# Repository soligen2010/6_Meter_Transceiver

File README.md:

# 6_Meter_Transceiver
A homebrew transceiver for the 6 meter Ham band
 
This project is work in progress.

## 2022-2-27 Status
 
This is my 6 Meter homebrew transceiver, currently work in progress.  It is a single conversion super –heterodyne design.  I constructed each stage independently with SMA connectors.  This is so I can re-make sections as needed, and will allow me in the future to swap sections to experiment with alternate designs.  The VFO and BFO are controlled using a SI5351 with an Arduino micro controller.  I currently have separate SI5351 modules for VFO and BFO because I suspected issues with cross-talk.  These issues may not actually be real, so once I am happy with the performance, I will test again with just one module to see if it is OK.  The Power Amp is still on the to-do list, so output is well under 0 DBm

The Blue boards were designed by me and ordered on-line.  The other boards I etched myself.  Construction is mostly surface mount because I find it easier than drilling all the holes.  SMD components are mostly 805 and 1206 size. Transistors are SOT23.

The Band Pass filter is a 5 coil design made with air-core inductors.

3 bi-directional termination insensitive (TIA) amps are used (blue boards).  Total RX gain is about 44db.  Total TX gain is about 16db.  Each board has its own independent RX/TX switching circuitry (mosfet based) and is fed with +12.5, GND, and RX/TX logic signal from the Arduino (3V logic and up will work)
The Mixer and modulator are both Diode Ring mixers.

The 12 MHz SSB filter is a crystal ladder filter similar to the one used in the uBitx.

The Mic and audio pre-amp (also a blue board) is made on a modified TIA amp board.  I had 10 of these boards made, and the needed circuitry was largely the same, so I modified the board with a rotary tool and jumpers.

The Audio amp is a PAM8403 module and drives a headset.  I did make some modifications to the module so it runs in-spec and to eliminate the power on audio pop.

The challenges I have been having are mostly related to spurs, splatter, carrier suppression and TX audio quality.  I have been gradually tweaking these things to improve operation before I start on a power amp.  My IF is 12 MHZ, and I was using the LSB side of the crystal filter because it is sharper (VFO 62 – 66 MHz) but have recently changed over to the USB side of the filter (VFO 38 – 42 MHz).  This eliminated the spurs I was seeing near the pass band.  I still need to make some adjustments to the crystal filter as it is too broad.

I still have some splatter and audio quality seems low, but I am starting to doubt my test setup.  I see the splatter on the RTL SDR, but I don’t see it on the Tiny SA.  The spatter happens at ~160 KHz intervals.  I am hoping to find someone local with a better spectrum analyzer to help me verify if it is the rig or my SDR dongle/test setup.

The modules to the side of the picture are my rejects/experiments.  The one covered in copper shows how I eventually will shield all the modules.  I 3D printed a cover for the board, then wrapped it with copper tape, soldered to the bottom ground plane.  The one shown is a diode ring modulator.  For some unknown reason the carrier suppression is rather poor.  I had previously made a junk-box modulator that had much better carrier suppression.  I don’t know why it is better than the one I more carefully made for the radio, but until I figure it out, I am using the junk box version.  The junk box modulator uses unmatched schottkey diodes, whereas the “final” one uses a 4 diode SMD package because I wanted them matched – I thought this would be better, but maybe not.

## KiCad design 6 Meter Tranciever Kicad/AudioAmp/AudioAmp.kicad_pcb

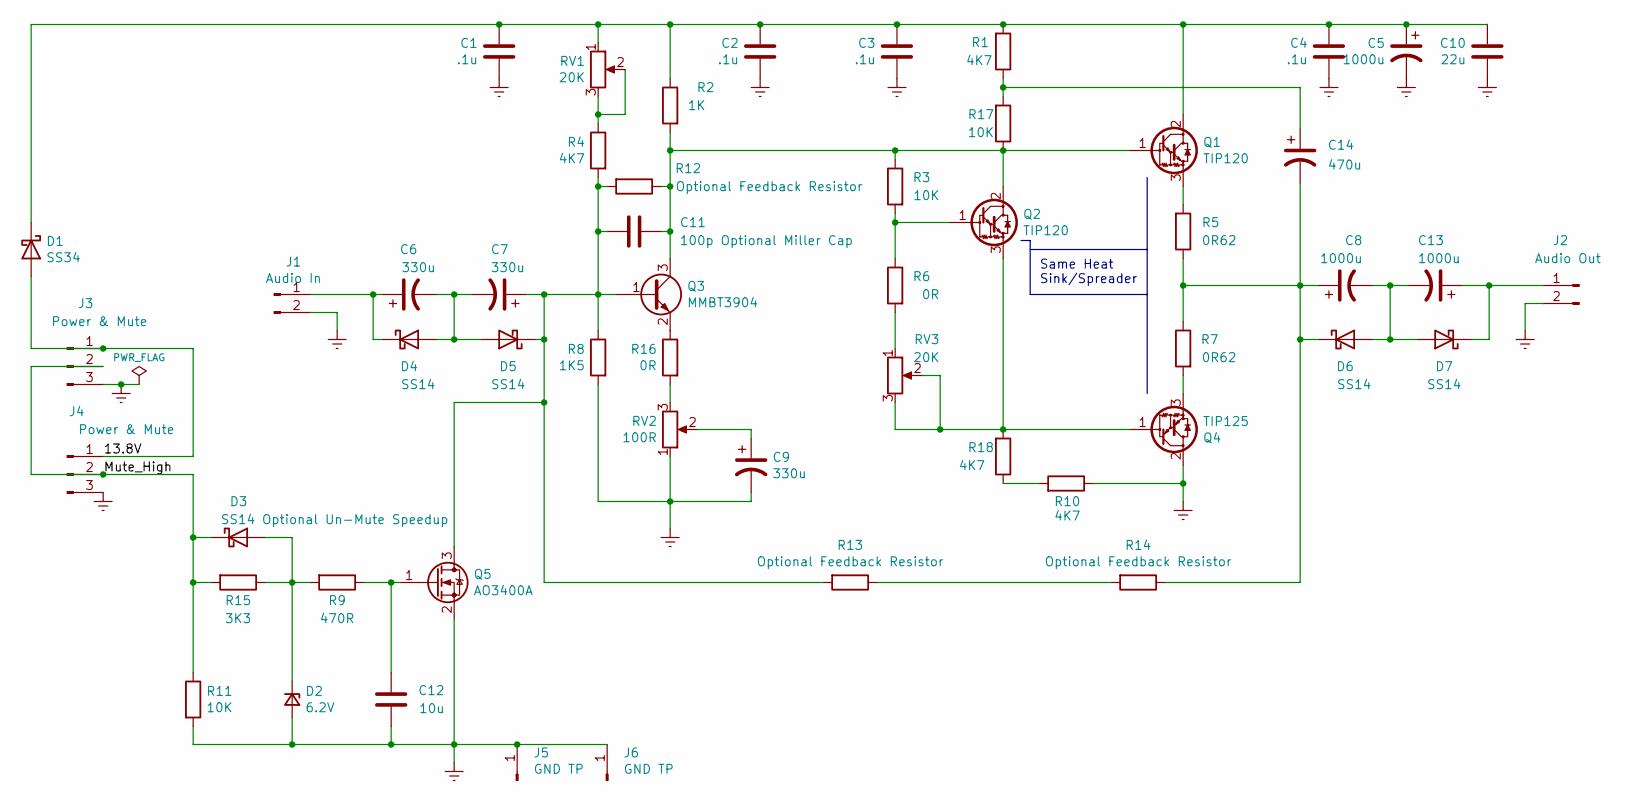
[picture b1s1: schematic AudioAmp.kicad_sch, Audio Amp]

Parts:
C1, C2, C3, C4: .1u; SMD_Combo_1206_0805
C5: 1000u; CP_Radial_D18.0mm_P7.50mm
C6, C7, C9: 330u; CP_Radial_D13.0mm_P5.00mm
C8, C13: 1000u; CP_Radial_D13.0mm_P5.00mm
C10: 22u; SMD_Combo_1206_0805
C11: 100p Optional Miller Cap; SMD_Combo_1206_0805
C12: 10u; SMD_Combo_1206_0805
C14: 470u; CP_Radial_D13.0mm_P5.00mm
D1: SS34; D_SMA_Handsoldering
D2: 6.2V; D_MiniMELF_Handsoldering
D3: SS14 Optional Un-Mute Speedup; D_SMA_Handsoldering
D4, D5, D6, D7: SS14; D_SMA_Handsoldering
J1: Audio In; Molex_KK-254_AE-6410-02A_1x02_P2.54mm_Vertical
J2: Audio Out; Molex_KK-254_AE-6410-02A_1x02_P2.54mm_Vertical
J3, J4: Power & Mute; FanPinHeader_1x03_P2.54mm_Vertical
J5, J6: GND TP; PinHeader_1x01_P2.54mm_Vertical
Q1, Q2: TIP120; TO-220-3_Vertical
Q3: MMBT3904; SOT-23_Handsoldering
Q4: TIP125; TO-220-3_Vertical
Q5: AO3400A; SOT-23_Handsoldering
R1, R4, R10, R18: 4K7; SMD_Combo_1206_0805
R2: 1K; SMD_Combo_1206_0805
R3, R11, R17: 10K; SMD_Combo_1206_0805
R5, R7: 0R62; R_Axial_DIN0309_L9.0mm_D3.2mm_P12.70mm_Horizontal
R6, R16: 0R; SMD_Combo_1206_0805
R8: 1K5; SMD_Combo_1206_0805
R9: 470R; SMD_Combo_1206_0805
R12, R13, R14: Optional Feedback Resistor; SMD_Combo_1206_0805
R15: 3K3; SMD_Combo_1206_0805
RV1, RV3: 20K; Potentiometer_Piher_PT-6-V_Vertical
RV2: 100R; Potentiometer_Piher_PT-6-V_Vertical

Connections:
/13.8V: D1.2 (A), J3.1, J4.1
/Mute_High: D3.1 (K), J3.2, J4.2, R11.1, R15.2
GNDREF: C1.2, C2.2, C3.2, C4.2, C5.2, C9.2, C10.2, C12.2, D2.2 (A), J1.2, J2.2, J3.3, J4.3, J5.1, J6.1, Q4.2 (C), Q5.2 (S), R8.2, R10.1, R11.2, RV2.1
unnamed: C1.1, C2.1, C3.1, C4.1, C5.1, C10.1, D1.1 (K), Q1.2 (C), R1.2, R2.1, RV1.1
unnamed: C6.1, D4.1 (K), J1.1
unnamed: C6.2, C7.2, D4.2 (A), D5.2 (A)
unnamed: C8.1, C14.2, D6.1 (K), R5.1, R7.1, R14.1
unnamed: C9.1, RV2.2
unnamed: C11.1, Q1.1 (B), Q2.2 (C), Q3.3 (C), R2.2, R3.1, R12.1, R17.1
unnamed: C7.1, C11.2, D5.1 (K), Q3.1 (B), Q5.3 (D), R4.2, R8.1, R12.2, R13.2
unnamed: C12.1, Q5.1 (G), R9.1
unnamed: C13.1, D7.1 (K), J2.1
unnamed: C8.2, C13.2, D6.2 (A), D7.2 (A)
unnamed: C14.1, R1.1, R17.2
unnamed: D2.1 (K), D3.2 (A), R9.2, R15.1
unnamed: Q1.3 (E), R5.2
unnamed: Q2.1 (B), R3.2, R6.1
unnamed: Q2.3 (E), Q4.1 (B), R18.2, RV3.2, RV3.3
unnamed: Q3.2 (E), R16.1
unnamed: Q4.3 (E), R7.2
unnamed: R4.1, RV1.2, RV1.3
unnamed: R6.2, RV3.1
unnamed: R10.2, R18.1
unnamed: R13.1, R14.2
unnamed: R16.2, RV2.3

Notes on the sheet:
Same Heat Sink/Spreader

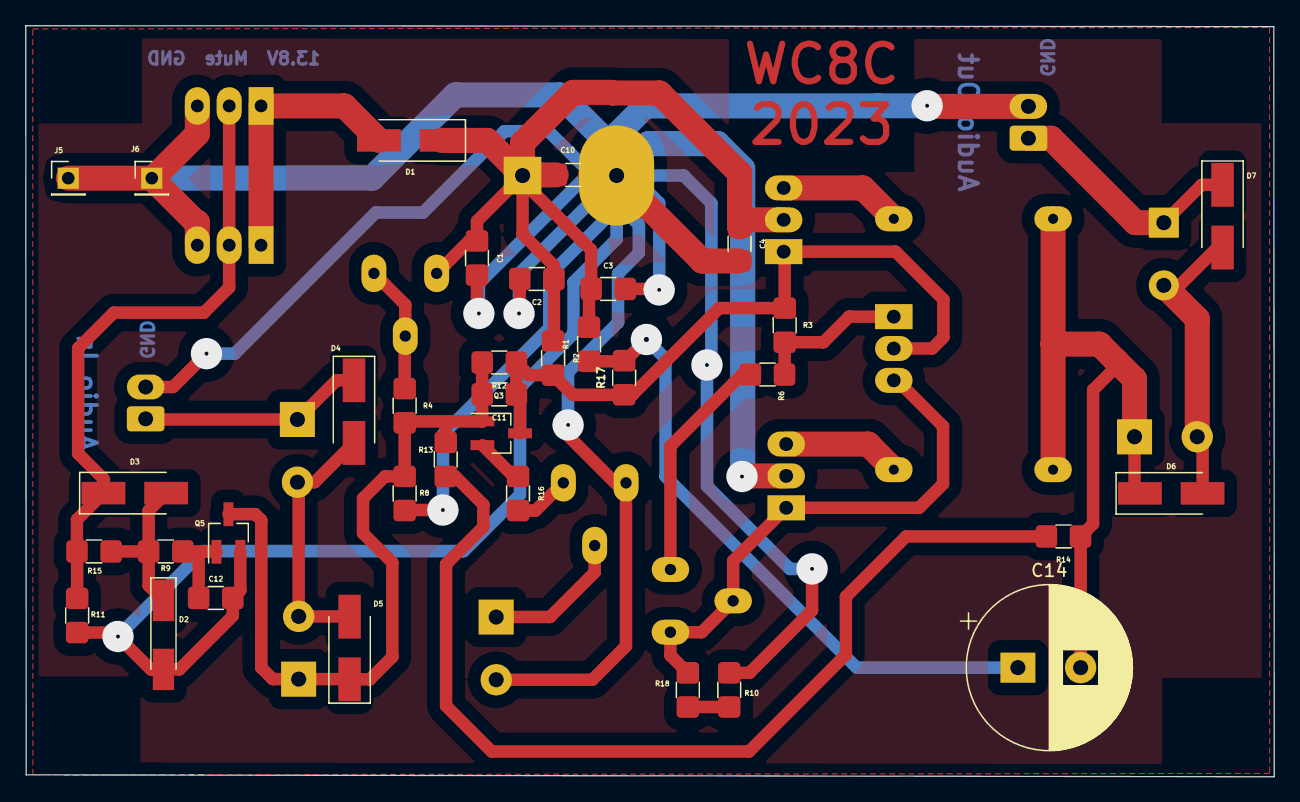
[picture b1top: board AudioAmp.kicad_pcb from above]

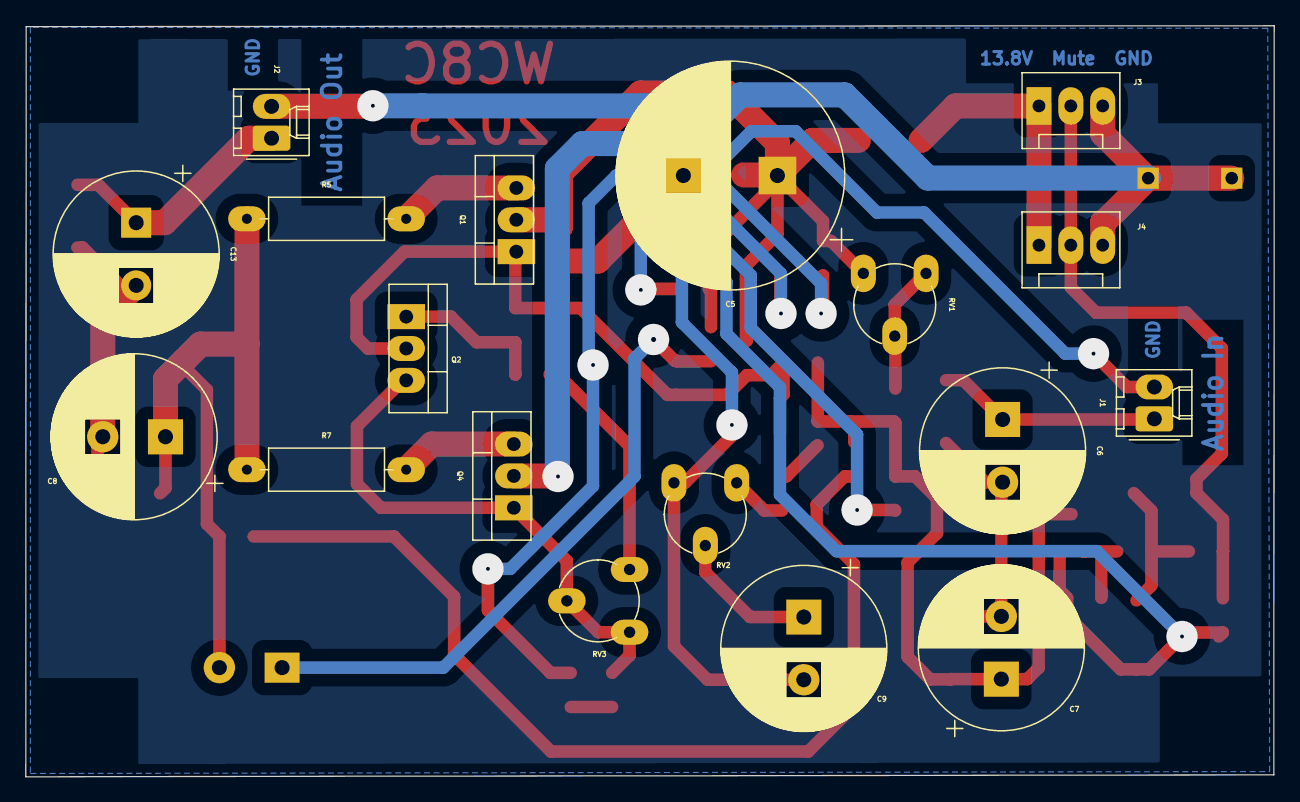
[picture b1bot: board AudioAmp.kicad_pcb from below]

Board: 2 copper layers, 99.5 x 59.9 mm, 53 parts (18 on the bottom side), 25 nets.

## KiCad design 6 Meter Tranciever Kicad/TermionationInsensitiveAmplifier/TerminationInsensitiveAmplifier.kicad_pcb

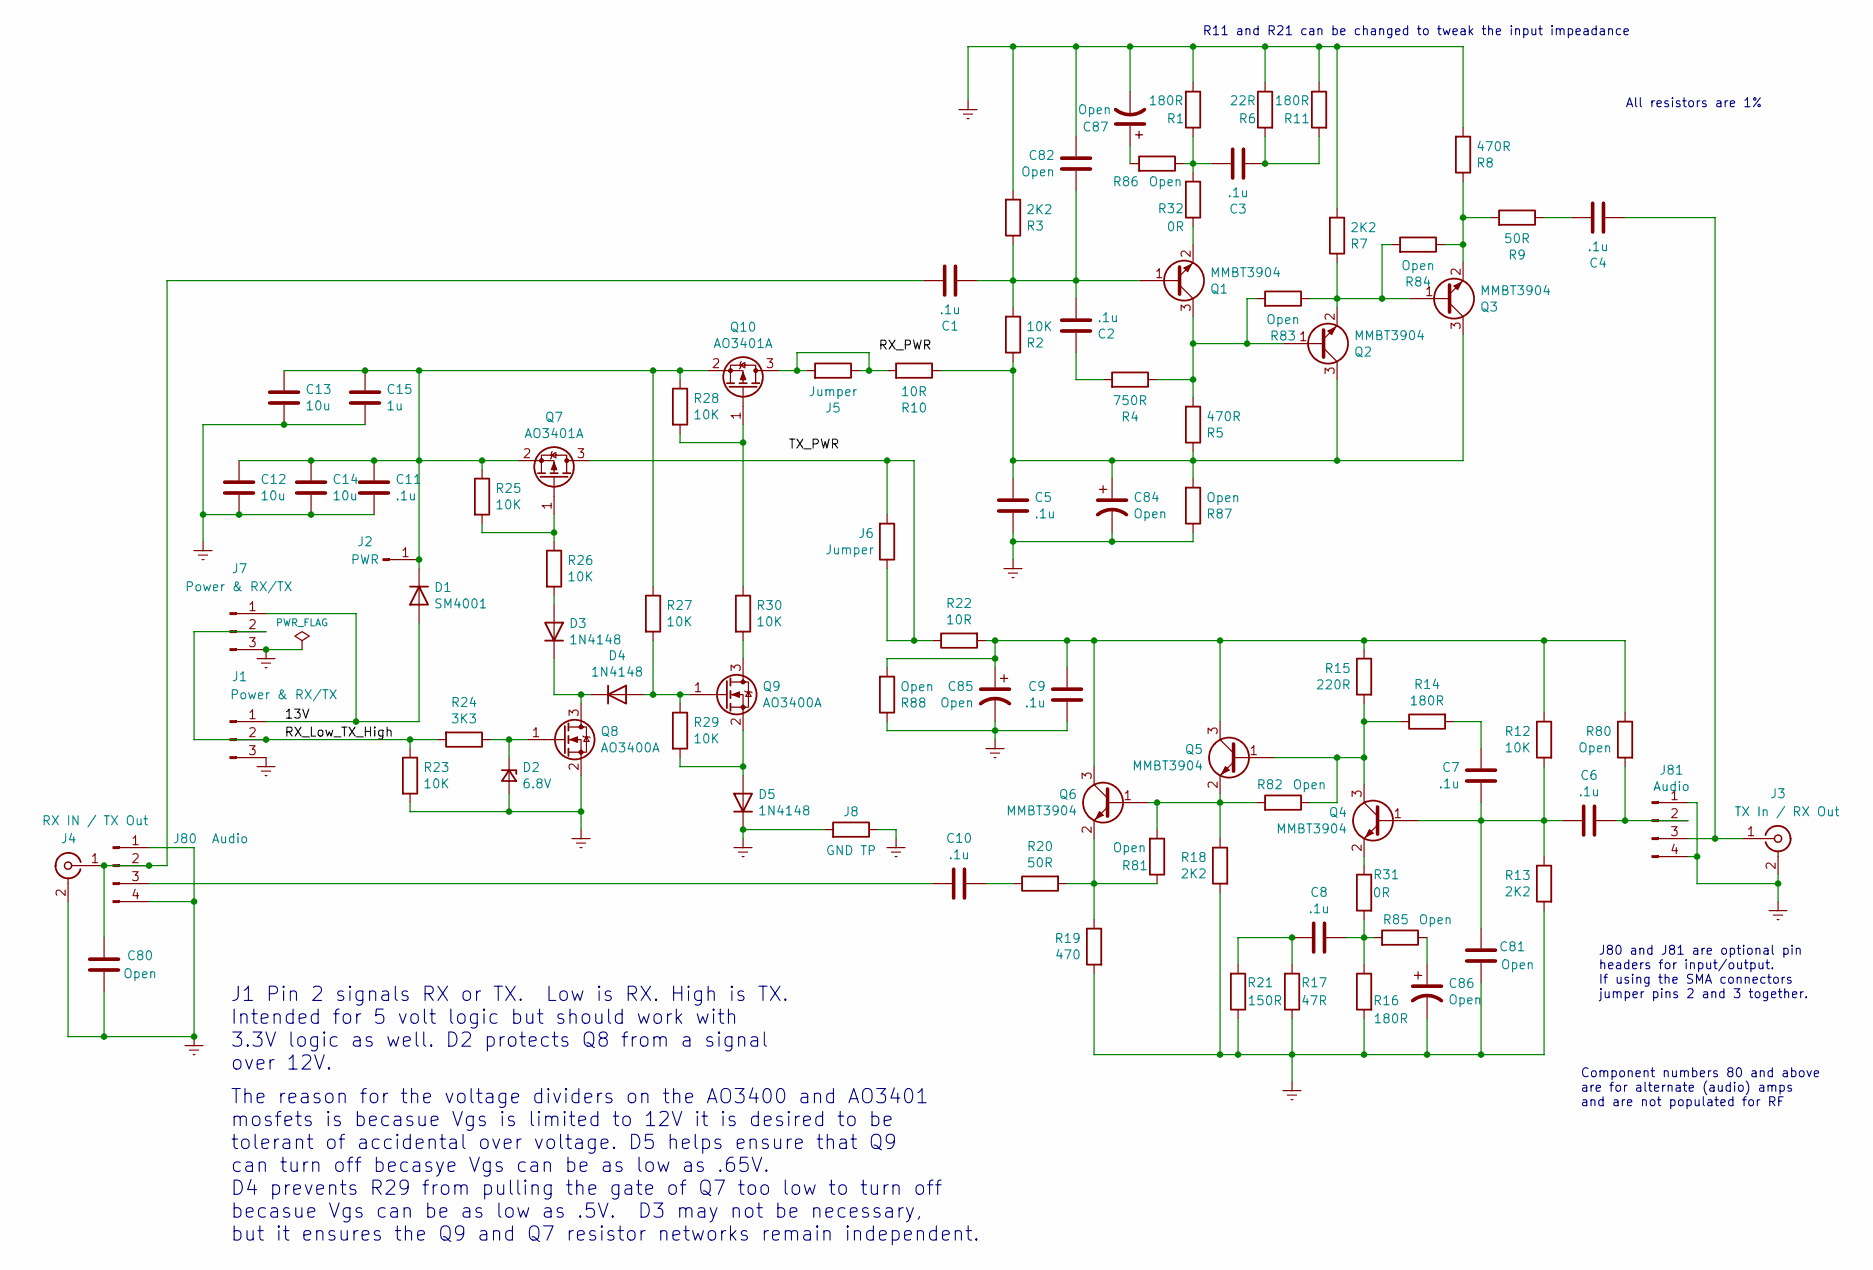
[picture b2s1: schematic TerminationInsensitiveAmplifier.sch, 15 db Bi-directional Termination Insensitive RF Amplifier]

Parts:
C1, C4, C6, C10: .1u; Cap_0805_1206_6032
C2, C3, C5, C7, C8, C9, C11: .1u; SMD_Combo_1206_0805
C12, C13, C14: 10u; SMD_Combo_1206_0805
C15: 1u; SMD_Combo_1206_0805
C80, C81, C82: Open; SMD_Combo_1206_0805
C84, C85, C86, C87: Open; Cap_0805_1206_6032
D1: SM4001; D_SMA_Handsoldering
D2: 6.8V; D_MiniMELF_Handsoldering
D3, D4, D5: 1N4148; D_SOD-323_HandSoldering
J1, J7: Power & RX/TX; FanPinHeader_1x03_P2.54mm_Vertical
J2: PWR; PinHeader_1x01_P2.54mm_Vertical
J3: TX In / RX Out; SMA_Molex_73251-2120_EdgeMount_Horizontal
J4: RX IN / TX Out; SMA_Molex_73251-2120_EdgeMount_Horizontal
J5, J6: Jumper; R_Axial_DIN0207_L6.3mm_D2.5mm_P7.62mm_Horizontal
J8: GND TP; R_Axial_DIN0207_L6.3mm_D2.5mm_P7.62mm_Horizontal
J80, J81: Audio; PinSocket_1x04_P2.54mm_Vertical
Q1, Q2, Q3, Q4, Q5, Q6: MMBT3904; SOT-23_Handsoldering
Q7, Q10: AO3401A; SOT-23_Handsoldering
Q8, Q9: AO3400A; SOT-23_Handsoldering
R1, R11, R14, R16: 180R; SMD_Combo_1206_0805
R2, R12, R23, R25, R26, R27, R28, R29, R30: 10K; SMD_Combo_1206_0805
R3, R7, R13, R18: 2K2; SMD_Combo_1206_0805
R4: 750R; SMD_Combo_1206_0805
R5, R8: 470R; SMD_Combo_1206_0805
R6: 22R; SMD_Combo_1206_0805
R9, R20: 50R; SMD_Combo_1206_0805
R10, R22: 10R; SMD_Combo_1206_0805
R15: 220R; SMD_Combo_1206_0805
R17: 47R; SMD_Combo_1206_0805
R19: 470; SMD_Combo_1206_0805
R21: 150R; SMD_Combo_1206_0805
R24: 3K3; SMD_Combo_1206_0805
R31, R32: 0R; SMD_Combo_1206_0805
R80, R81, R82, R83, R84, R85, R86, R87, R88: Open; SMD_Combo_1206_0805

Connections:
/13V: D1.2 (A), J1.1, J7.1
/RX_Low_TX_High: J1.2, J7.2, R23.1, R24.2
GNDREF: C5.2, C9.2, C11.2, C12.2, C13.2, C14.2, C15.2, C80.1, C81.2, C82.1, C84.2, C85.2, C86.2, C87.2, D2.2 (A), D5.1 (K), J1.3, J3.2 (Ext), J4.2 (Ext), J7.3, J8.1, J8.2, J80.1, J80.4, J81.1, J81.4, Q8.2 (S), R1.2, R3.2, R6.1, R7.2, R8.2, R11.1, R13.2, R16.2, R17.1, R18.2, R19.2, R21.1, R23.2, R87.1, R88.1; also elsewhere on the board
unnamed: C1.1, C2.2, C82.2, Q1.1 (B), R2.2, R3.1
unnamed: C1.2, C80.2, J4.1 (In), J80.2
unnamed: C2.1, R4.2
unnamed: C3.1, R6.2, R11.2
unnamed: C3.2, R1.1, R32.2, R86.1
unnamed: C4.1, J3.1 (In), J81.3
unnamed: C4.2, R9.1
unnamed 10: C5.1, C84.1, Q2.3 (C), Q3.3 (C), R2.1, R5.1, R10.1, R87.2; also elsewhere on the board
unnamed: C6.1, C7.2, C81.1, Q4.1 (B), R12.2, R13.1
unnamed: C6.2, J81.2, R80.2
unnamed: C7.1, R14.2
unnamed: C8.1, R17.2, R21.2
unnamed: C8.2, R16.1, R31.2, R85.2
unnamed: C10.1, J80.3
unnamed: C10.2, R20.1
unnamed: C11.1, C12.1, C13.1, C14.1, C15.1, D1.1 (K), J2.1, Q7.2 (S), Q10.2 (S), R25.1, R27.1, R28.1
unnamed 19: C9.1, C85.1, Q5.3 (C), Q6.3 (C), R12.1, R15.1, R22.2, R80.1, R88.2; also elsewhere on the board
unnamed 20: C86.1, R85.1; also elsewhere on the board
unnamed 21: C87.1, R86.2; also elsewhere on the board
unnamed: D2.1 (K), Q8.1 (G), R24.1
unnamed: D3.1 (K), D4.1 (K), Q8.3 (D)
unnamed: D3.2 (A), R26.2
unnamed: D4.2 (A), Q9.1 (G), R27.2, R29.1
unnamed: D5.2 (A), Q9.2 (S), R29.2
unnamed: J5.1, J5.2, Q10.3 (D), R10.2
unnamed: J6.1, J6.2, Q7.3 (D), R22.1
unnamed: Q1.2 (E), R32.1
unnamed: Q1.3 (C), Q2.1 (B), R4.1, R5.2, R83.2
unnamed: Q2.2 (E), Q3.1 (B), R7.1, R83.1, R84.2
unnamed: Q3.2 (E), R8.1, R9.2, R84.1
unnamed: Q4.2 (E), R31.1
unnamed: Q4.3 (C), Q5.1 (B), R14.1, R15.2, R82.1
unnamed: Q5.2 (E), Q6.1 (B), R18.1, R81.2, R82.2
unnamed: Q6.2 (E), R19.1, R20.2, R81.1
unnamed: Q7.1 (G), R25.2, R26.1
unnamed: Q9.3 (D), R30.2
unnamed: Q10.1 (G), R28.2, R30.1

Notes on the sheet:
The reason for the voltage dividers on the AO3400 and AO3401 mosfets is becasue Vgs is limited to 12V it is desired to be tolerant of accidental over voltage. D5 helps ensure that Q9 can turn off becasye Vgs can be as low as .65V. D4 prevents R29 from pulling the gate of Q7 too low to turn off beca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
J1 Pin 2 signals RX or TX. Low is RX. High is TX. Intended for 5 volt logic but should work with 3.3V logic as well. D2 protects Q8 from a signal over 12V.
R11 and R21 can be changed to tweak the input impeadance
All resistors are 1%
J80 and J81 are optional pin headers for input/output. If using the SMA connectors jumper pins 2 and 3 together.
Component numbers 80 and above are for alternate (audio) amps and are not populated for RF

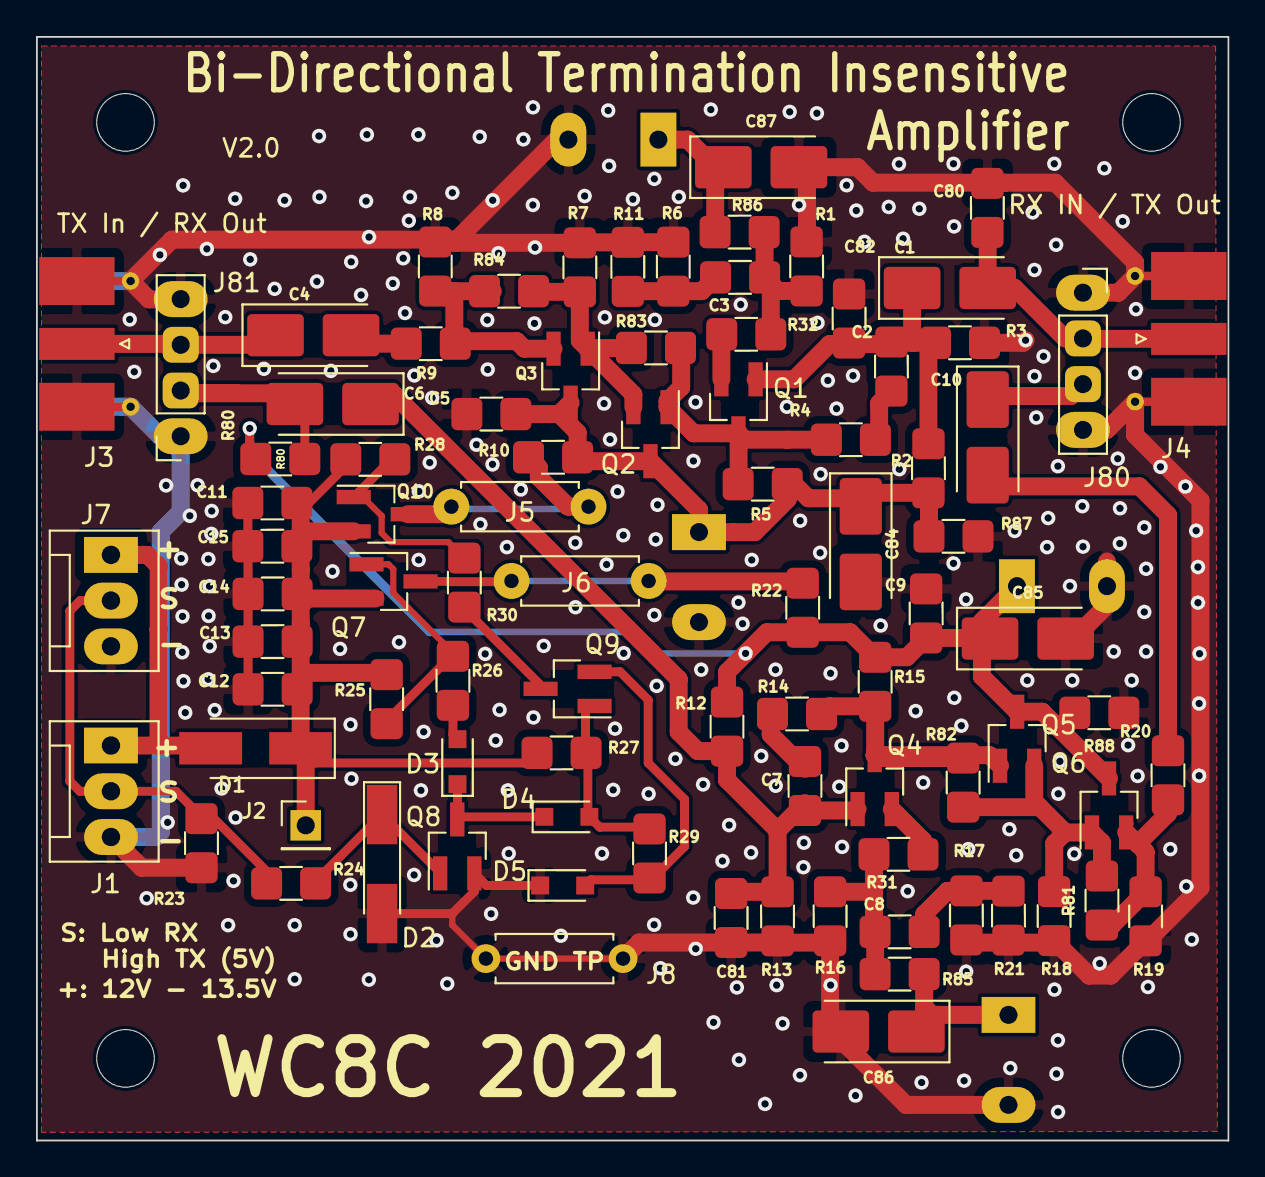
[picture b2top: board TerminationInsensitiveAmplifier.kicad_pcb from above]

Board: 2 copper layers, 66.2 x 61.3 mm, 96 parts (0 on the bottom side), 40 nets.

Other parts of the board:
 : 5mm_Pads
 #2,  #3,  #4: 5mm_Pads
 #5,  #6,  #7,  #8: MountingHole_3.2mm_M3

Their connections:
GNDREF: .2, #2.2, #3.2, #4.2; also elsewhere on the board
unnamed 10: .1; also elsewhere on the board
unnamed 19: #2.1; also elsewhere on the board
unnamed 20: #4.1; also elsewhere on the board
unnamed 21: #3.1; also elsewhere on the board

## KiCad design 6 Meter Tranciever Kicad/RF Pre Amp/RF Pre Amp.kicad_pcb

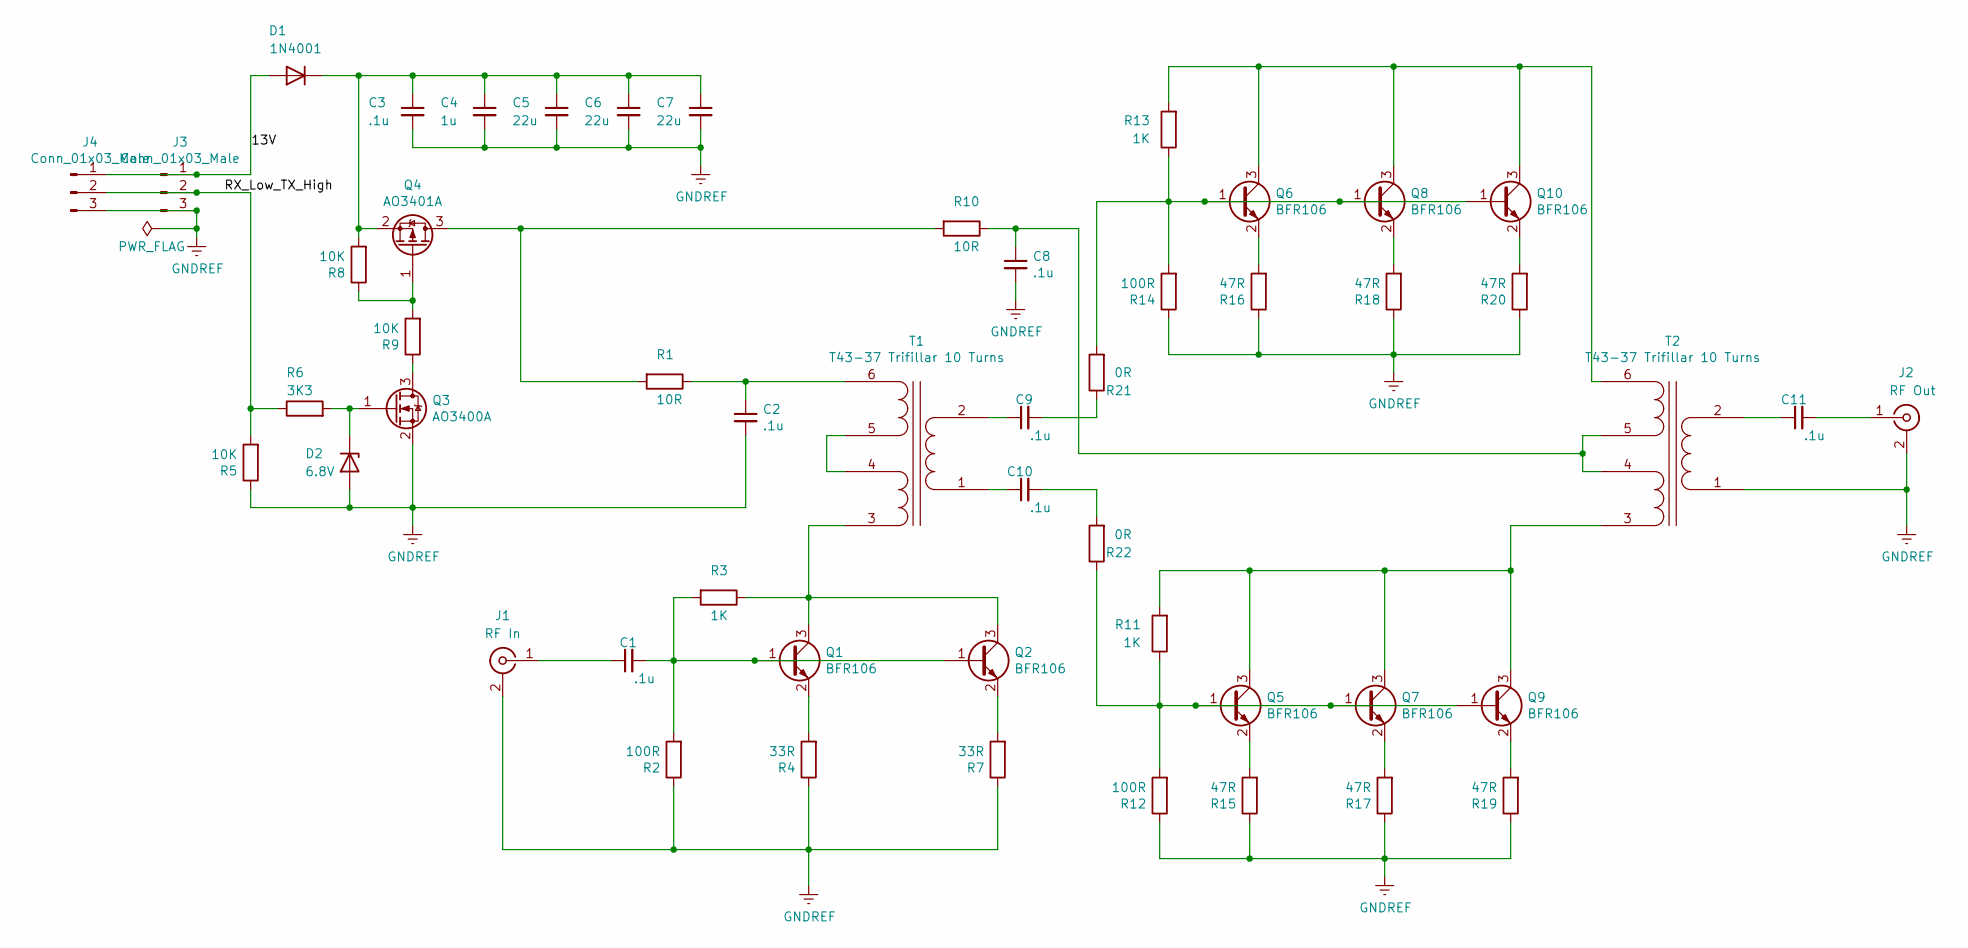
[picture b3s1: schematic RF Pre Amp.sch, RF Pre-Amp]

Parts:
C1, C2, C3, C8, C9, C10, C11: .1u; SMD_Combo_1206_0805
C4: 1u; SMD_Combo_1206_0805
C5, C6, C7: 22u; SMD_Combo_1206_0805
D1: 1N4001; D_2114_3652Metric_Pad1.85x3.75mm_HandSolder
D2: 6.8V; D_MiniMELF_Handsoldering
J1: RF In; SMA_Molex_73251-2120_EdgeMount_Horizontal
J2: RF Out; SMA_Molex_73251-2120_EdgeMount_Horizontal
J3, J4: Conn_01x03_Male; FanPinHeader_1x03_P2.54mm_Vertical
Q1, Q2, Q5, Q6, Q7, Q8, Q9, Q10: BFR106; SOT-323_SC-70_Handsoldering
Q3: AO3400A; SOT-323_SC-70_Handsoldering
Q4: AO3401A; SOT-323_SC-70_Handsoldering
R1, R10: 10R; SMD_Combo_1206_0805
R2, R12, R14: 100R; SMD_Combo_1206_0805
R3, R11, R13: 1K; SMD_Combo_1206_0805
R4, R7: 33R; SMD_Combo_1206_0805
R5, R8, R9: 10K; SMD_Combo_1206_0805
R6: 3K3; SMD_Combo_1206_0805
R15, R16, R17, R18, R19, R20: 47R; SMD_Combo_1206_0805
R21, R22: 0R; SMD_Combo_1206_0805
T1, T2: T43-37 Trifillar 10 Turns; T37_Trifillar

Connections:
/13V: D1.2 (A), J3.1, J4.1
/RX_Low_TX_High: J3.2, J4.2, R5.2, R6.1
GNDREF: C2.2, C3.2, C4.2, C5.2, C6.2, C7.2, C8.2, D2.2 (A), J1.2 (Ext), J2.2 (Ext), J3.3, J4.3, Q3.2 (S), R2.1, R4.1, R5.1, R7.1, R12.1, R14.1, R15.1, R16.1, R17.1, R18.1, R19.1, R20.1, T2.1 (AA)
unnamed: C1.1, J1.1 (In)
unnamed: C1.2, Q1.1 (B), Q2.1 (B), R2.2, R3.2
unnamed: C2.1, R1.1, T1.6 (SD)
unnamed: C3.1, C4.1, C5.1, C6.1, C7.1, D1.1 (K), Q4.2 (S), R8.2
unnamed: C8.1, R10.1, T2.4 (SB), T2.5 (SC)
unnamed: C9.1, T1.2 (AB)
unnamed: C9.2, R21.1
unnamed: C10.1, T1.1 (AA)
unnamed: C10.2, R22.2
unnamed: C11.1, T2.2 (AB)
unnamed: C11.2, J2.1 (In)
unnamed: D2.1 (K), Q3.1 (G), R6.2
unnamed: Q1.2 (E), R4.2
unnamed: Q1.3 (C), Q2.3 (C), R3.1, T1.3 (SA)
unnamed: Q2.2 (E), R7.2
unnamed: Q3.3 (D), R9.1
unnamed: Q4.1 (G), R8.1, R9.2
unnamed: Q4.3 (D), R1.2, R10.2
unnamed: Q5.1 (B), Q7.1 (B), Q9.1 (B), R11.1, R12.2, R22.1
unnamed: Q5.2 (E), R15.2
unnamed: Q5.3 (C), Q7.3 (C), Q9.3 (C), R11.2, T2.3 (SA)
unnamed: Q6.2 (E), R16.2
unnamed: Q7.2 (E), R17.2
unnamed: Q8.2 (E), R18.2
unnamed: Q9.2 (E), R19.2
unnamed: Q6.1 (B), Q8.1 (B), Q10.1 (B), R13.1, R14.2, R21.2
unnamed: Q10.2 (E), R20.2
unnamed: Q6.3 (C), Q8.3 (C), Q10.3 (C), R13.2, T2.6 (SD)
unnamed: T1.4 (SB), T1.5 (SC)

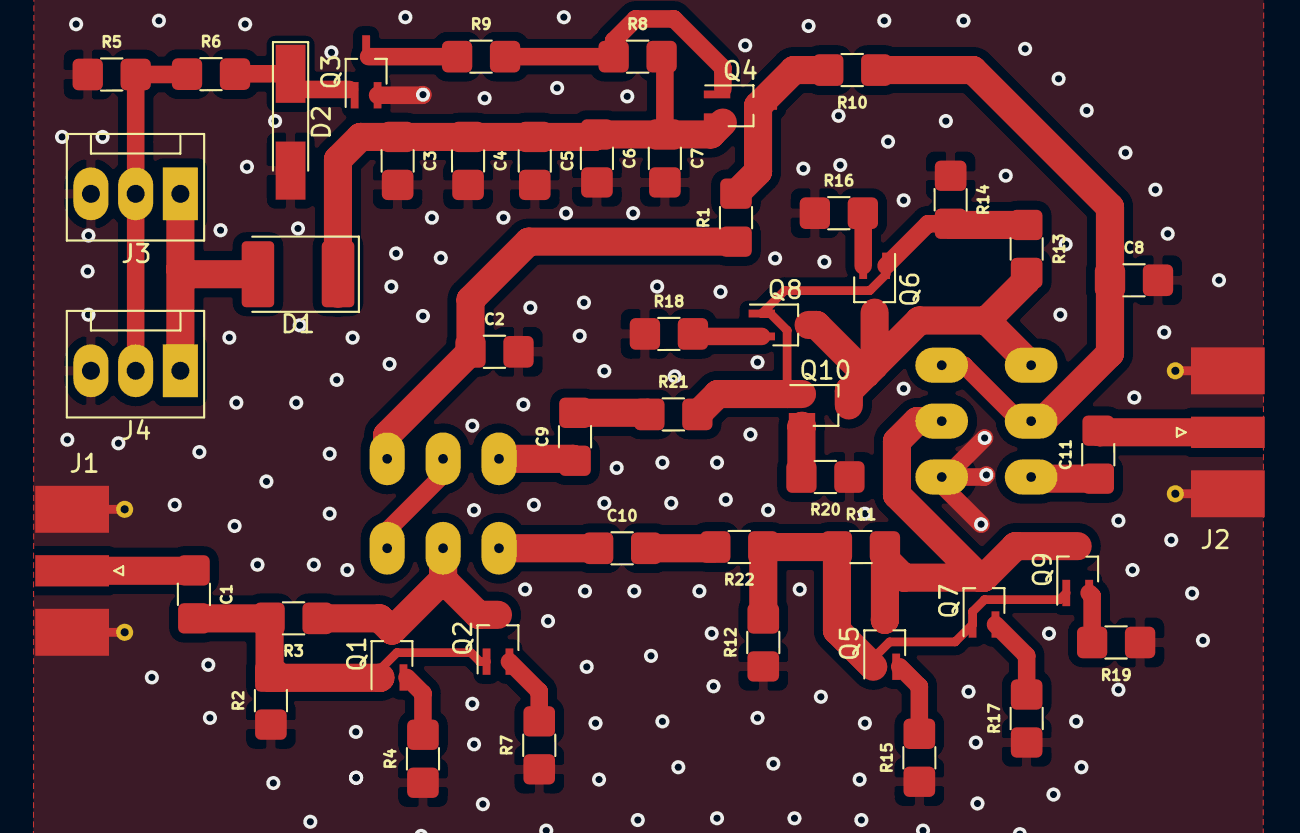
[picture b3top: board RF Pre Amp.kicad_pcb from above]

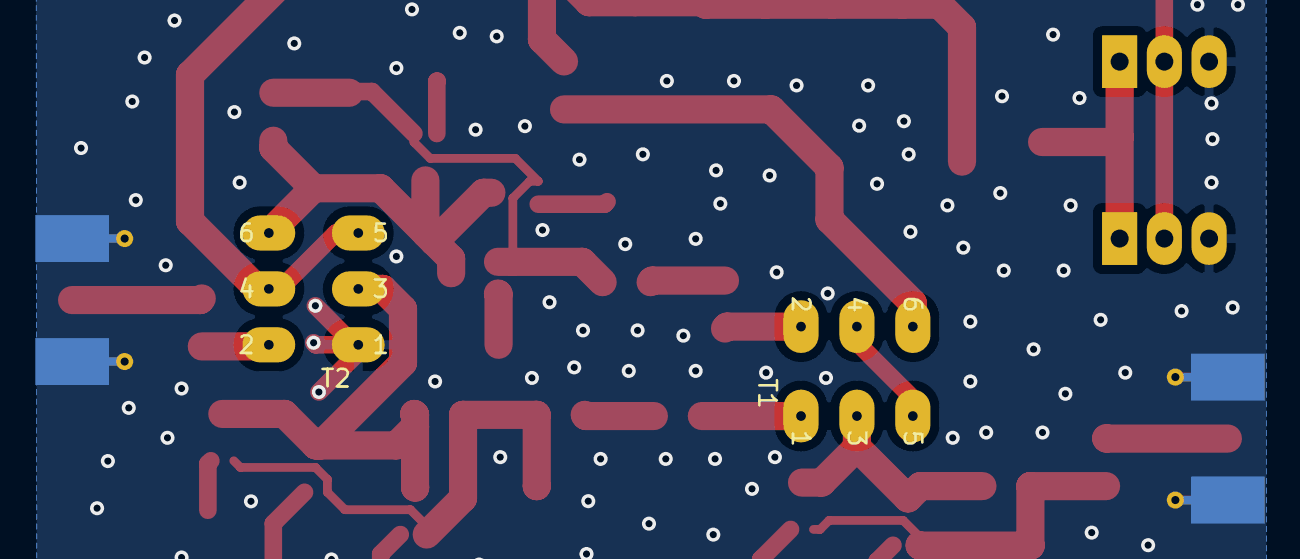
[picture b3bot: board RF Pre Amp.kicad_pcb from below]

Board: 2 copper layers, 51 parts (2 on the bottom side), 32 nets.

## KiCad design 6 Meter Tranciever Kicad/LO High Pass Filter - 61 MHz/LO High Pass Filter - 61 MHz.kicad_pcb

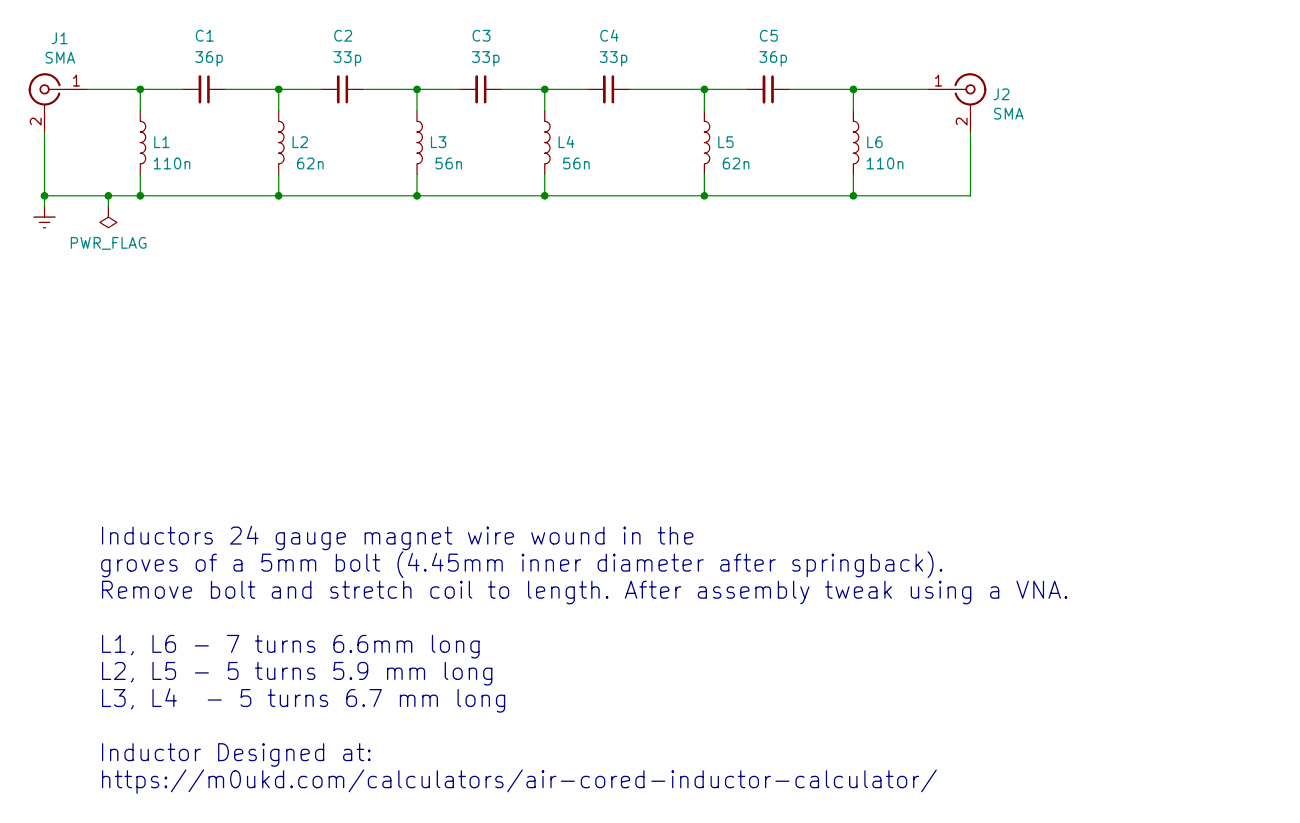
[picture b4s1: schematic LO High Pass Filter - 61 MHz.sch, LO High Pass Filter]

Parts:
C1, C5: 36p; SMD_Combo_1206_0805
C2, C3, C4: 33p; SMD_Combo_1206_0805
J1, J2: SMA; SMA_Molex_73251-2120_EdgeMount_Horizontal
L1, L6: 110n; Air_Inductor_6.75mm
L2, L5: 62n; Air_Inductor_6.75mm
L3, L4: 56n; Air_Inductor_6mm

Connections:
GNDREF: J1.2 (Ext), J2.2 (Ext), L1.2, L2.2, L3.2, L4.2, L5.2, L6.2
unnamed: C1.1, C2.2, L2.1
unnamed: C1.2, J1.1 (In), L1.1
unnamed: C2.1, C3.2, L3.1
unnamed: C3.1, C4.2, L4.1
unnamed: C4.1, C5.2, L5.1
unnamed: C5.1, J2.1 (In), L6.1

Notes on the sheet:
Inductors 24 gauge magnet wire wound in the groves of a 5mm bolt (4.45mm inner diameter after springback). Remove bolt and stretch coil to length. After assembly tweak using a VNA. L1, L6 - 7 turns 6.6mm long L2, L5 - 5 turns 5.9 mm long L3, L4 - 5 turns 6.7 mm long Inductor Designed at: https://m0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

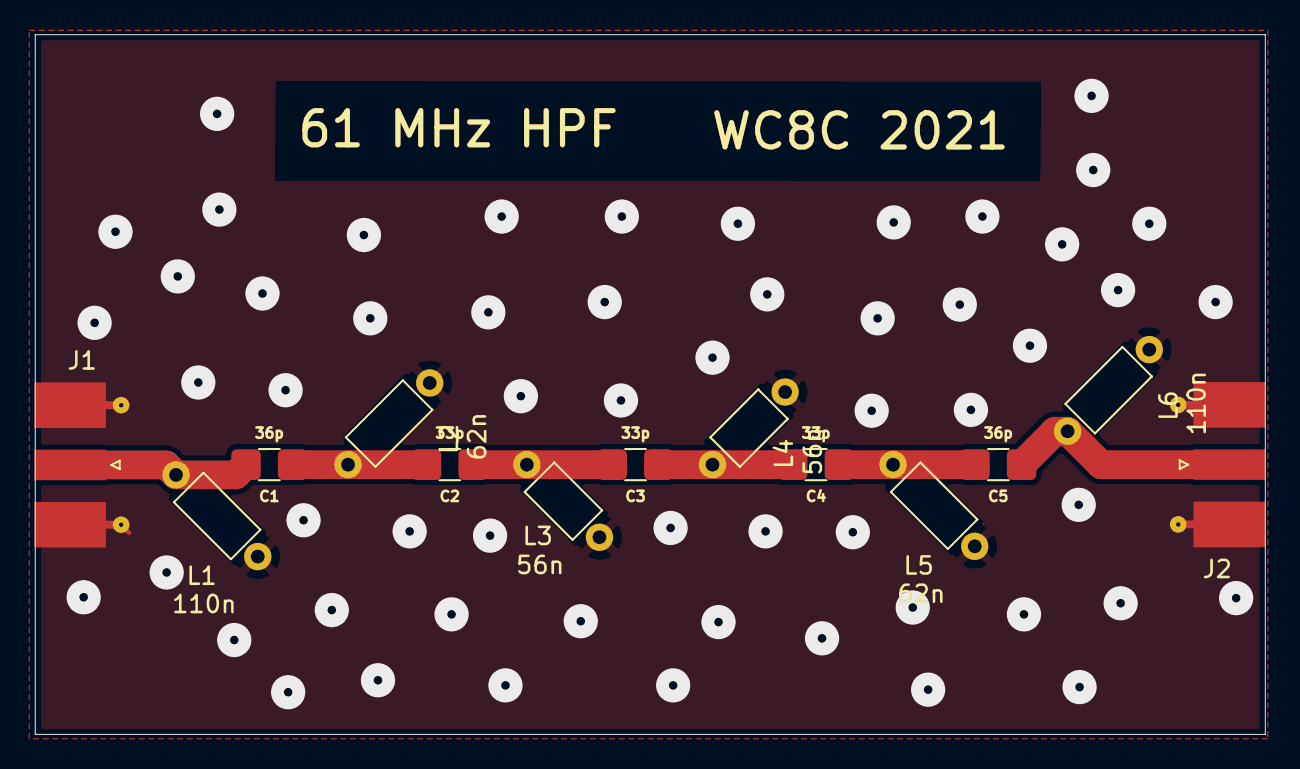
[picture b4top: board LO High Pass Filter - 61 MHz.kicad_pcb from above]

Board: 2 copper layers, 71.9 x 40.9 mm, 13 parts (0 on the bottom side), 7 nets.

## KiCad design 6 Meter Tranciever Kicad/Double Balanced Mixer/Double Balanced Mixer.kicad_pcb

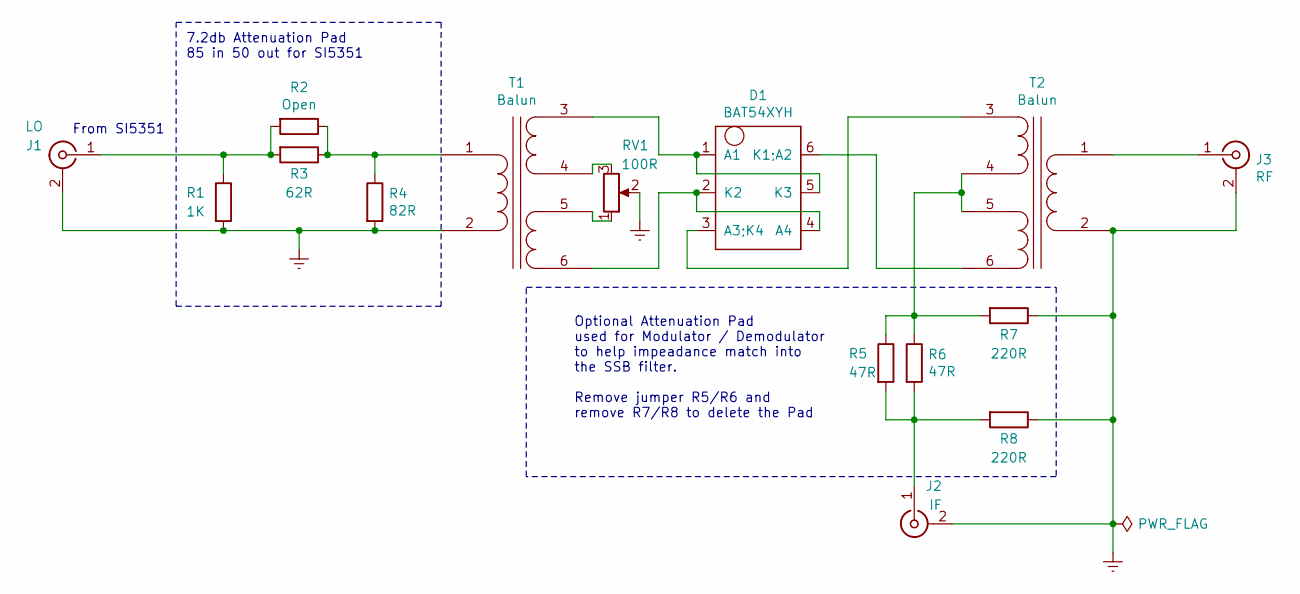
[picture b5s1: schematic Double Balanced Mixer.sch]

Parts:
D1: BAT54XYH; SOT-363_SC-70-6_Handsoldering
J1: LO; SMA_Molex_73251-2120_EdgeMount_Horizontal
J2: IF; SMA_Molex_73251-2120_EdgeMount_Horizontal
J3: RF; SMA_Molex_73251-2120_EdgeMount_Horizontal
R1: 1K; SMD_Combo_1206_0805
R2: Open; SMD_Combo_1206_0805
R3: 62R; SMD_Combo_1206_0805
R4: 82R; SMD_Combo_1206_0805
R5, R6: 47R; SMD_Combo_1206_0805
R7, R8: 220R; SMD_Combo_1206_0805
RV1: 100R; Potentiometer_Piher_PT-6-V_Vertical
T1, T2: Balun; T37_Trifillar

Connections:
GNDREF: J1.2 (Ext), J2.2 (Ext), J3.2 (Ext), R1.2, R4.2, R7.1, R8.1, RV1.2, T1.2 (AB), T2.2 (AB)
unnamed: D1.1 (A1), D1.5 (K3), T1.3 (SA)
unnamed: D1.2 (K2), D1.4 (A4), T1.6 (SD)
unnamed: D1.3 (A3;K4), T2.3 (SA)
unnamed: D1.6 (K1;A2), T2.6 (SD)
unnamed: J1.1 (In), R1.1, R2.2, R3.2
unnamed: J2.1 (In), R5.2, R6.2, R8.2
unnamed: J3.1 (In), T2.1 (AA)
unnamed: R2.1, R3.1, R4.1, T1.1 (AA)
unnamed: R5.1, R6.1, R7.2, T2.4 (SB), T2.5 (SC)
unnamed: RV1.1, T1.5 (SC)
unnamed: RV1.3, T1.4 (SB)

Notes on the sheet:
7.2db Attenuation Pad 85 in 50 out for SI5351
From SI5351
Optional Attenuation Pad used for Modulator / Demodulator to help impeadance match into the SSB filter. Remove jumper R5/R6 and remove R7/R8 to delete the Pad

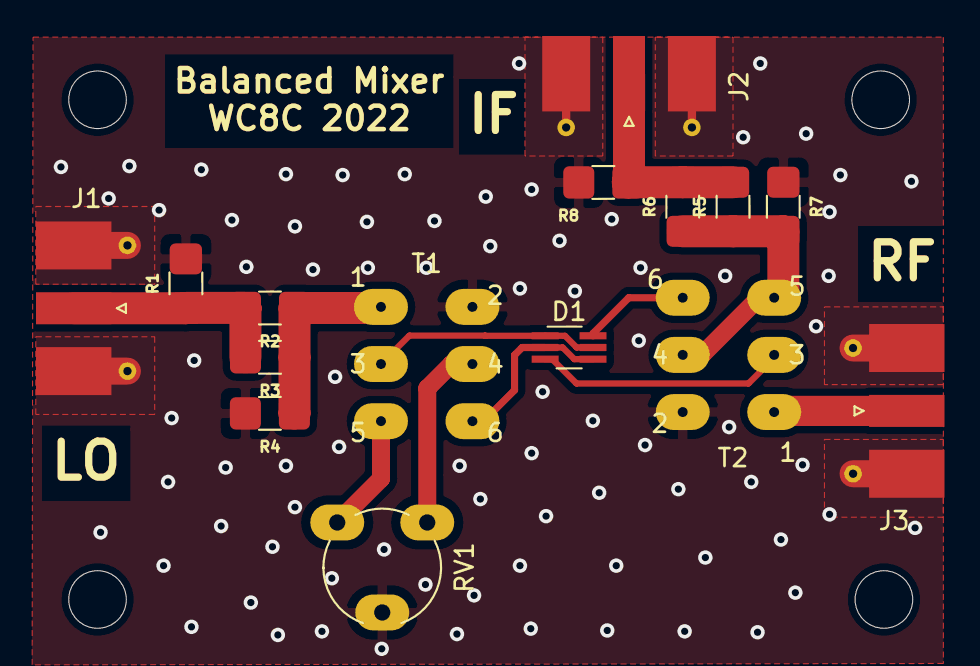
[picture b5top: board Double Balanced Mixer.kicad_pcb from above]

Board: 2 copper layers, 19 parts (0 on the bottom side), 12 nets.

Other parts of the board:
 : MountingHole_3.2mm_M3
 #2,  #3,  #4: MountingHole_3.2mm_M3
